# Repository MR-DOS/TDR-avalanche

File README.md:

# TDR-avalanche
----
## Description
Simple flat-top avalanche pulser with integrated power supply for the avalanche transistor circuit and trigger circuitry. 

----
## Overview
This pulser was made in hope to use it to measure reflections on cables. However, using the transistor 2SC5773, it was not possible to obtain faster risetime than about 700 ps. This allows to measure reflections, but the resolution is quite limited due to the shape of the pulse (slow risetime and a backlash after the falling edge). Maybe using some other transistor and changing the compensation circuitry, it could be made better. Since there are many PECL buffers with rise and fall times faster than 200 ps (and reproducible), the next one will use some IC to generate the pulses. Also, generating short rectangular pulse is not very good if you want to postprocess the data, because you would need to run a decorrelation to find out what is happening on the cable. Using a long rectangular pulse (with infinitesimally fast edges) where all of the reflected energy comes back before the falling edge allows you to derive the signal which in turn gives you impulse response.

----
## Features
### Power supplies
The pulser contains a 40V power supply followed by denoising network and 6V - 35V regulated linear supply to set the avalanche voltage. The whole board is powered from 5V using Mini USB-B, consuming less than 100 mA.

### Avalanche pulser
The avalanche pulser uses 2SC5773 transistor (6V NPN, fT=10.8 GHz @ 50 mA). The compensation circuitry makes the output pulse a nice clean rectangular pulse with a flat top with no visible ringing (invisible with 1 GHz oscilloscope, to be precise), however there is a not very nice backlash after the falling edge (see pictures). The transistor does not self-avalanche when set properly, it has to be triggered by external source. I used 8-10 kHz triggering during the development and use. There are 2 SMA connectors, one for coaxial cable where energy for the pulse is stored (length of the cable determines length of the pulse) and one where the pulses are output.

### Trigger circuitry
The trigger circuitry triggers avalanche on rising edge of the input trigger signal. There is RC circuit which sets the time between the trigger and avalanche. However, it seems to have quite large jitter. There is also trigger output which you can connect to scilloscope (the avalanche happens on falling edge of the TRIG OUT). The trigger circuitry can be inhibited using the jumper JP1 when tuning the avalanche voltage.

### Attenuators
There are 2 attenuator sections giving 11.3 and 7.9 dB attenuation. The first one is mandatory as it is an impedance matching circuit. The second one is just a normal attenuator and can be omitted.

----
## How to use it as a simple standalone time-domain reflectometer
Connect square wave generator to the SYNC\_IN port. Connect an oscilloscope to the SYNC\_OUT port and to the PULSE\_OUT port.
Connect the coaxial cable to be measured to the STORAGE_COAX port. The cable MUST NOT have any shorts in it or any low impedance termination, because it is connected to the collector network and it would load the 200k resistor and the transistor would not avalanche. This severely limits the useability, so this mode is not recommended.

----
## How to use it as a pulser for general use
Connect square wave generator to the SYNC\_IN port.
Connect storage coaxial cable to the STORAGE_COAX port. You should use some 50 Ohm cable with low losses, ideally some rigid or semirigid cable. I used RG-174 because I had a lot of it on hand and the circuit is tweaked for use with the RG-174 (I used about one meter of the cable which gave me about 8 ns long pulse). Connect the PULSE\_OUT port to anything you want (50 Ohm terminated).

----
## Images
Oscillogram of the whole pulse:

Oscillogram of the rising edge:

Oscillogram of the zoomed in pulse:

Picture of the made and assembled PCB:

Picture of the PCB connected to oscilloscope and generator:

----
## Reference
[AN-94: Slew Rate Verification for Wideband Amplifiers](https://www.analog.com/media/en/technical-documentation/application-notes/an94f.pdf)

[AN-72: A Seven-Nanosecond Comparator for Single Supply Operation](https://www.analog.com/media/en/technical-documentation/application-notes/an72f.pdf)

[Tweet with photo of the etched PCB](https://twitter.com/polasek_petr/status/1063875099940532225)

[Tweet with photos of the etched, drilled and assembled PCB](https://twitter.com/polasek_petr/status/1064328075725426688)

[Tweet with measured output of the circuit](https://twitter.com/polasek_petr/status/1064698462539866112)

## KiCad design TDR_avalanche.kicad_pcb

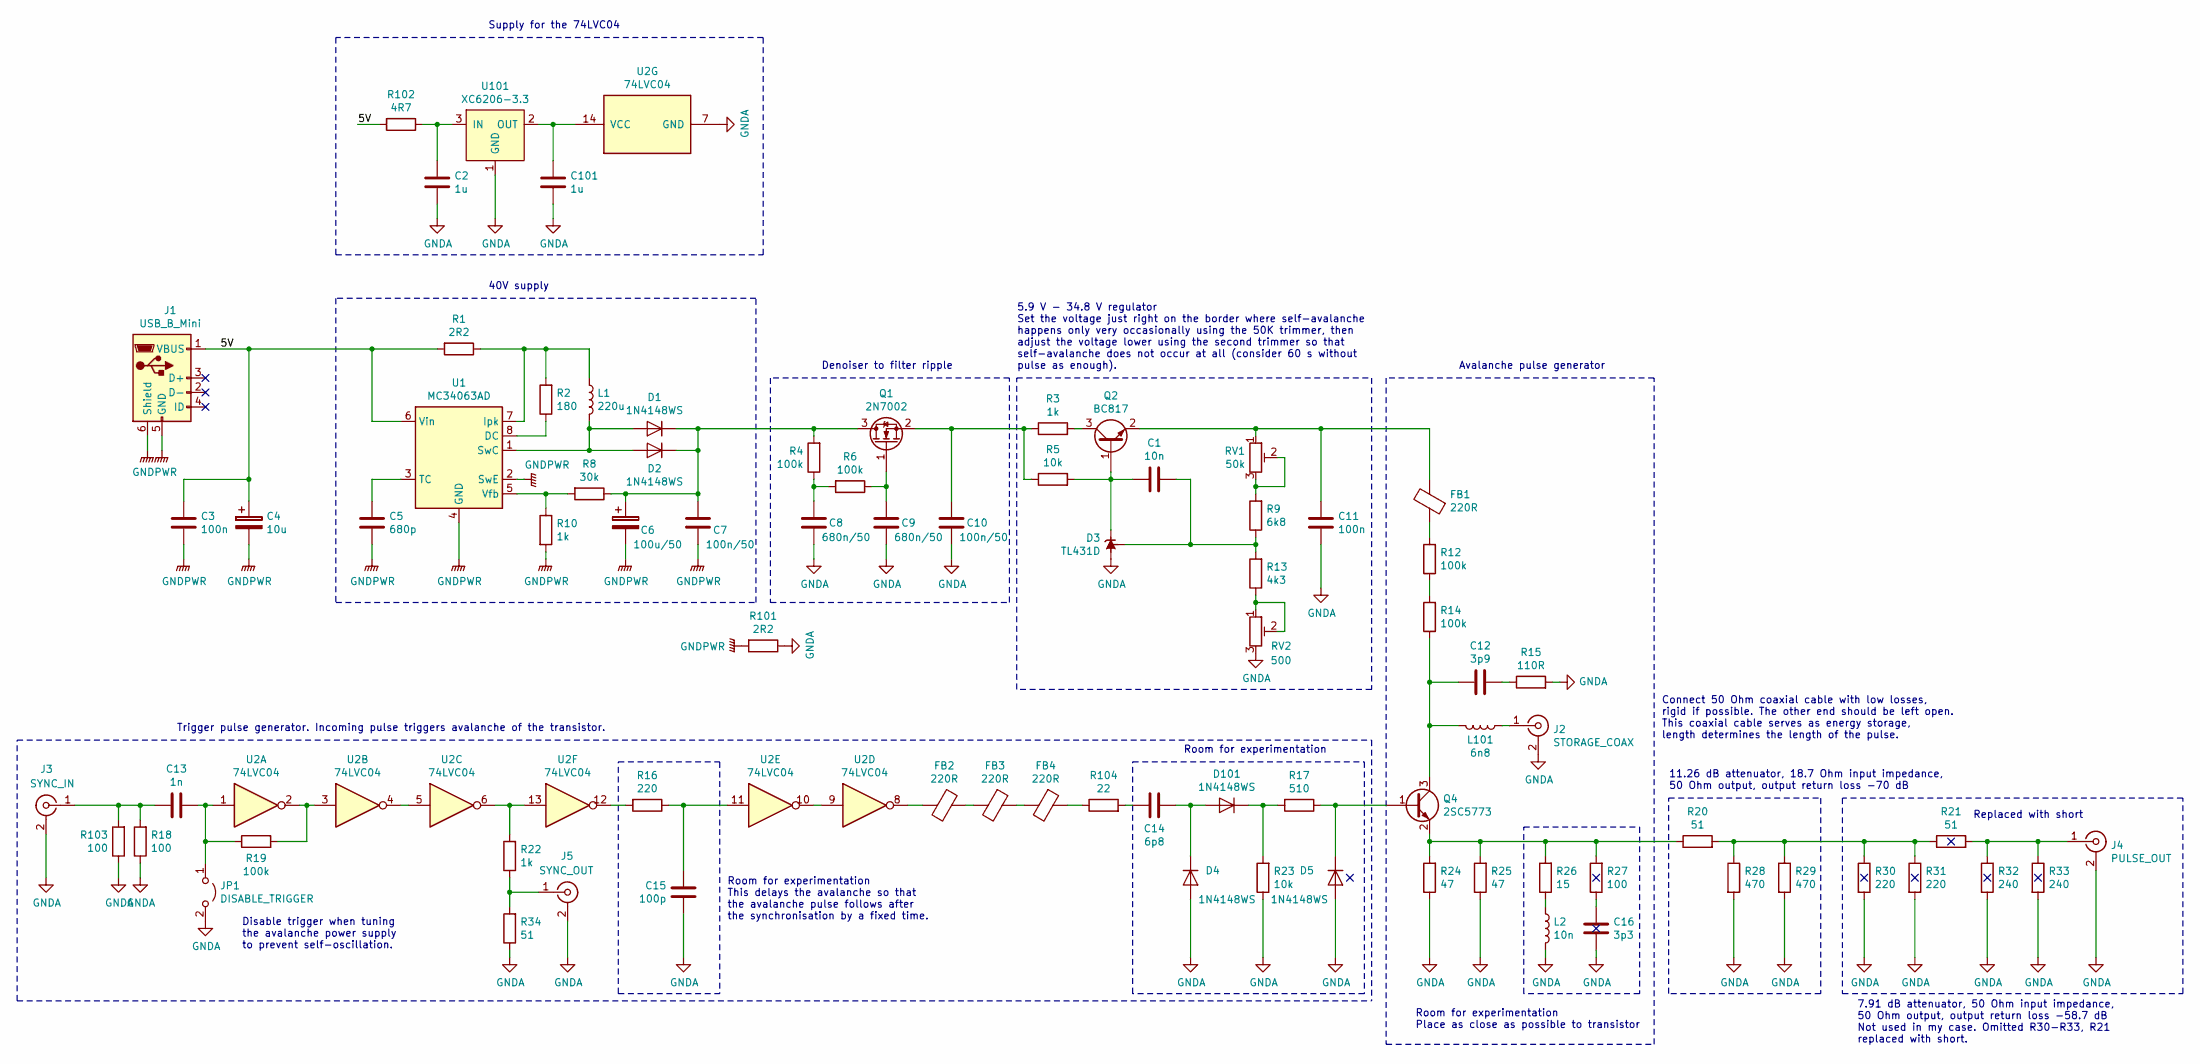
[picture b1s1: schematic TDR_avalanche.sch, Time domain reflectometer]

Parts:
C1: 10n; C_0805_2012Metric_Pad1.15x1.40mm_HandSolder
C2, C101: 1u; C_0805_2012Metric_Pad1.15x1.40mm_HandSolder
C3, C11: 100n; C_0805_2012Metric_Pad1.15x1.40mm_HandSolder
C4: 10u; CP_Elec_4x5.3
C5: 680p; C_0805_2012Metric_Pad1.15x1.40mm_HandSolder
C6: 100u/50; CP_Elec_8x6.9
C7, C10: 100n/50; C_0805_2012Metric_Pad1.15x1.40mm_HandSolder
C8, C9: 680n/50; C_0805_2012Metric_Pad1.15x1.40mm_HandSolder
C12: 3p9; C_0805_2012Metric_Pad1.15x1.40mm_HandSolder
C13: 1n; C_0805_2012Metric_Pad1.15x1.40mm_HandSolder
C14: 6p8; C_0805_2012Metric_Pad1.15x1.40mm_HandSolder
C15: 100p; C_0805_2012Metric_Pad1.15x1.40mm_HandSolder
C16: 3p3; C_0805_2012Metric_Pad1.15x1.40mm_HandSolder
D1, D2, D4, D5, D101: 1N4148WS; D_SOD-323_HandSoldering
D3: TL431D; SOIC-8_3.9x4.9mm_P1.27mm
FB1, FB2, FB3, FB4: 220R; L_0805_2012Metric_Pad1.15x1.40mm_HandSolder
J1: USB_B_Mini; USB_Mini-B_Lumberg_2486_01_Horizontal
J2: STORAGE_COAX; Molex_SMA_Jack_Edge_Mount_Chinese
J3: SYNC_IN; Molex_SMA_Jack_Edge_Mount_Chinese
J4: PULSE_OUT; Molex_SMA_Jack_Edge_Mount_Chinese
J5: SYNC_OUT; Molex_SMA_Jack_Edge_Mount_Chinese
JP1: DISABLE_TRIGGER; PinHeader_1x02_P2.54mm_Vertical_SMD_Pin1Right
L1: 220u; L_7.3x7.3_H4.5
L2: 10n; L_0805_2012Metric_Pad1.15x1.40mm_HandSolder
L101: 6n8; L_0805_2012Metric_Pad1.15x1.40mm_HandSolder
Q1: 2N7002; SOT-23_Handsoldering
Q2: BC817; SOT-23_Handsoldering
Q4: 2SC5773; SC-59_Handsoldering
R1, R101: 2R2; R_0805_2012Metric_Pad1.15x1.40mm_HandSolder
R2: 180; R_0805_2012Metric_Pad1.15x1.40mm_HandSolder
R3, R10, R22: 1k; R_0805_2012Metric_Pad1.15x1.40mm_HandSolder
R4, R6, R12, R14, R19: 100k; R_0805_2012Metric_Pad1.15x1.40mm_HandSolder
R5, R23: 10k; R_0805_2012Metric_Pad1.15x1.40mm_HandSolder
R8: 30k; R_0805_2012Metric_Pad1.15x1.40mm_HandSolder
R9: 6k8; R_0805_2012Metric_Pad1.15x1.40mm_HandSolder
R13: 4k3; R_0805_2012Metric_Pad1.15x1.40mm_HandSolder
R15: 110R; R_0805_2012Metric_Pad1.15x1.40mm_HandSolder
R16, R30, R31: 220; R_0805_2012Metric_Pad1.15x1.40mm_HandSolder
R17: 510; R_0805_2012Metric_Pad1.15x1.40mm_HandSolder
R18, R27, R103: 100; R_0805_2012Metric_Pad1.15x1.40mm_HandSolder
R20, R21, R34: 51; R_0805_2012Metric_Pad1.15x1.40mm_HandSolder
R24, R25: 47; R_0805_2012Metric_Pad1.15x1.40mm_HandSolder
R26: 15; R_0805_2012Metric_Pad1.15x1.40mm_HandSolder
R28, R29: 470; R_0805_2012Metric_Pad1.15x1.40mm_HandSolder
R32, R33: 240; R_0805_2012Metric_Pad1.15x1.40mm_HandSolder
R102: 4R7; R_0805_2012Metric_Pad1.15x1.40mm_HandSolder
R104: 22; R_0805_2012Metric_Pad1.15x1.40mm_HandSolder
RV1: 50k; Potentiometer_Bourns_3296Y_Vertical
RV2: 500; Potentiometer_Bourns_3296Y_Vertical
U1: MC34063AD; SOIC-8_3.9x4.9mm_P1.27mm
U2: 74LVC04; SOIC-14_3.9x8.7mm_P1.27mm
U101: XC6206-3.3; SOT-23_Handsoldering

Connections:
/5V: C3.1, C4.1, J1.1 (VBUS), R1.2, R102.2, U1.6 (Vin)
GNDA: C2.2, C8.2, C9.2, C10.2, C11.2, C15.2, C16.1, C101.2, D3.2 (A), D3.3 (A), D3.6 (A), D3.7 (A), D4.2 (A), D5.2 (A), J2.2 (Ext), J3.2 (Ext), J4.2 (Ext), J5.2 (Ext), JP1.2 (B), L2.2, R15.2, R18.1, R23.1, R24.1, R25.1, R28.2, R29.2, R30.2, R31.2, R32.2, R33.2, R34.1, R101.1, R103.1, RV2.3, U2.7 (GND), U101.1 (GND)
GNDPWR: C3.2, C4.2, C5.2, C6.2, C7.2, J1.5 (GND), J1.6 (Shield), R10.2, R101.2, U1.2 (SwE), U1.4 (GND)
unnamed: C1.1, D3.8 (REF), R9.1, R13.2
unnamed: C1.2, D3.1 (K), Q2.1 (B), R5.2
unnamed: C2.1, R102.1, U101.3 (IN)
unnamed: C5.1, U1.3 (TC)
unnamed: C6.1, C7.1, D1.1 (K), D2.1 (K), Q1.3 (D), R4.2, R8.1
unnamed: C8.1, R4.1, R6.2
unnamed: C9.1, Q1.1 (G), R6.1
unnamed: C10.1, Q1.2 (S), R3.1, R5.1
unnamed: C11.1, FB1.2, Q2.2 (E), RV1.1
unnamed: C12.1, R15.1
unnamed: C12.2, L101.2, Q4.3, R14.1
unnamed: C13.1, JP1.1 (A), R19.1, U2.1
unnamed: C13.2, J3.1 (In), R18.2, R103.2
unnamed: C14.1, D4.1 (K), D101.2 (A)
unnamed: C14.2, R104.2
unnamed: C15.1, R16.1, U2.11
unnamed: C16.2, R27.1
unnamed: C101.1, U2.14 (VCC), U101.2 (OUT)
unnamed: D1.2 (A), D2.2 (A), L1.2, U1.1 (SwC)
unnamed: D5.1 (K), Q4.1, R17.1
unnamed: D101.1 (K), R17.2, R23.2
unnamed: FB1.1, R12.2
unnamed: FB2.1, FB3.2
unnamed: FB2.2, U2.8
unnamed: FB3.1, FB4.2
unnamed: FB4.1, R104.1
unnamed: J2.1 (In), L101.1
unnamed: J4.1 (In), R21.2, R32.1, R33.1
unnamed: J5.1 (In), R22.1, R34.2
unnamed: L1.1, R1.1, R2.2, U1.7 (Ipk)
unnamed: L2.1, R26.1
unnamed: Q2.3 (C), R3.2
unnamed: Q4.2, R20.1, R24.2, R25.2, R26.2, R27.2
unnamed: R2.1, U1.8 (DC)
unnamed: R9.2, RV1.2, RV1.3
unnamed: R8.2, R10.1, U1.5 (Vfb)
unnamed: R12.1, R14.2
unnamed: R13.1, RV2.1, RV2.2
unnamed: R16.2, U2.12
unnamed: R19.2, U2.2, U2.3
unnamed: R20.2, R21.1, R28.1, R29.1, R30.1, R31.1
unnamed: R22.2, U2.6, U2.13
unnamed: U2.4, U2.5
unnamed: U2.9, U2.10

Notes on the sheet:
11.26 dB attenuator, 18.7 Ohm input impedance, 50 Ohm output, output return loss -70 dB
Room for experimentation
Room for experimentation Place as close as possible to transistor
7.91 dB attenuator, 50 Ohm input impedance, 50 Ohm output, output return loss -58.7 dB Not used in my case. Omitted R30-R33, R21 replaced with short.
Room for experimentation This delays the avalanche so that the avalanche pulse follows after the synchronisation by a fixed time.
40V supply
Denoiser to filter ripple
5.9 V - 34.8 V regulator Set the voltage just right on the border where self-avalanche happens only very occasionally using the 50K trimmer, then adjust the voltage lower using the second trimmer so that self-avalanche does not occur at all (consider 60 s without pulse as enough).
Trigger pulse generator. Incoming pulse triggers avalanche of the transistor.
Avalanche pulse generator
Disable trigger when tuning the avalanche power supply to prevent self-oscillation.
Connect 50 Ohm coaxial cable with low losses, rigid if possible. The other end should be left open. This coaxial cable serves as energy storage, length determines the length of the pulse.
Replaced with short
Supply for the 74LVC04

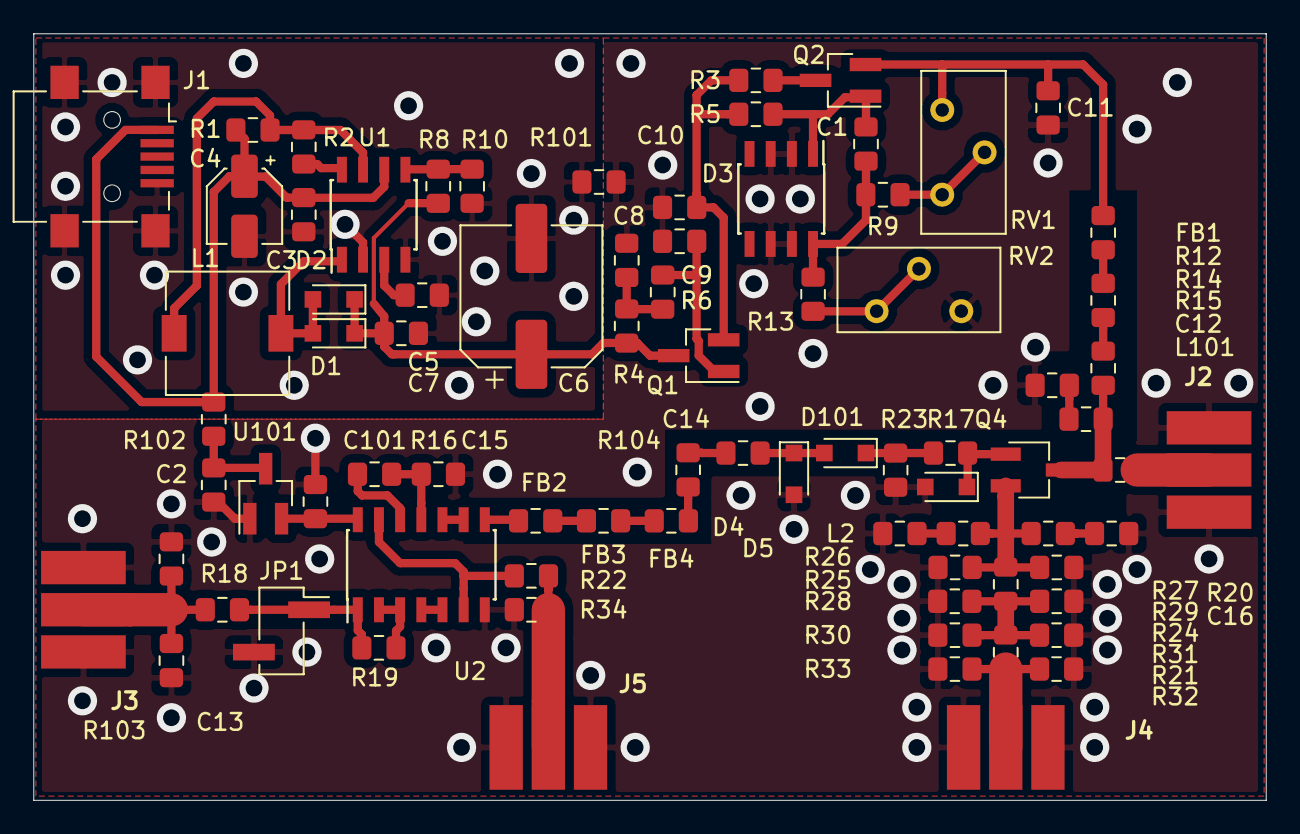
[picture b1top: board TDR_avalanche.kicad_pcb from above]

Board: 2 copper layers, 73.9 x 46.0 mm, 80 parts (0 on the bottom side), 47 nets.

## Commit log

2018-12-04 First published version
2018-12-04 Slight graphic changes to the text of README and a try to fix broken images
2018-12-04 Next try to fix images
2018-12-04 Last try to fix images because of a typo
2021-11-23 Create LICENSE
    Added GPLv3 license
